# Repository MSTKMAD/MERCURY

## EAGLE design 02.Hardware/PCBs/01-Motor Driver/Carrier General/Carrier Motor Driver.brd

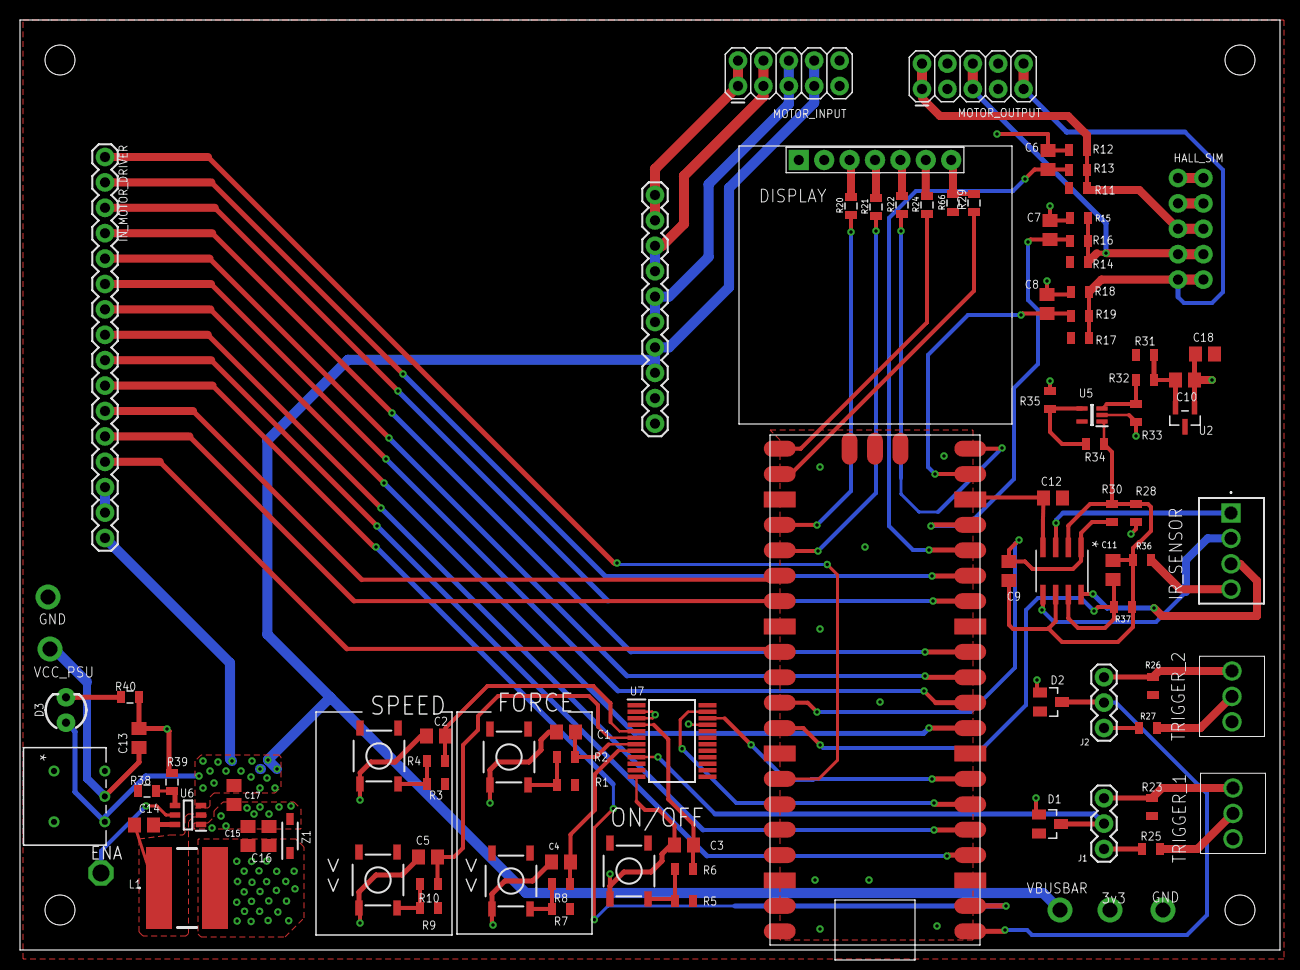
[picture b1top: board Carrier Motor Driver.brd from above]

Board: 2 copper layers, 126.0 x 93.0 mm, 88 parts (0 on the bottom side), 69 nets.

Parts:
C1, C2, C3, C4, C5, C6, C7, C8, C9, C10, C11, C12, C13, C14, C15, C16, C17, C18: C0805
D1, D2: BAT54S; SOT23
D3: LED_3MM
DISPLAY: Display; OLED_LCD
ENA: TESTPAD_TPSQPAD1-17; TESTPAD_P1-17
HALL_SIM: 2X5_NOSILK
IN_MOTOR_DRIVER: 1X16
IR_SENSOR: OSTVN04A150
J1, J2: 1X03
L1: SRN8040-8R2Y; SRN80408R2Y
MOTOR_INPUT: 2X5
MOTOR_OUTPUT: 2X5
OUT_MOTOR_DRIVER: 1X10
R1, R2, R3, R4, R5, R6, R7, R8, R9, R10, R11, R12, R13, R14, R15, R16, R17, R18, R19, R23, R25, R26, R27, R28, R30, R31, R32, R33, R34, R35, R36, R37: 0805
R20, R21, R22, R24, R29: 33; 0805
R38, R39, R40, R66: 10K; 0805
S1, S2, S3, S4, S5: MOMENTARY-SWITCH-SPST-SMD-5.2MM; TACTILE_SWITCH_SMD_5.2MM
TRIGGER_1, TRIGGER_2: OSTVN03A150
U1: MCP6002T-I/SN; SOIC8-N_MC_MCH
U2: LM4040BIM3-2.0/NOPB; DBZ3
U3: ATE1D-5M3-10-Z; SPDT05_ATE1D_9P5X8_NDC
U4: RPI_PICO
U5: MCP6001T-I_LT; SOT65P210X110-5N
U6: AP62200WU-7; SOT95P280X100-6N
U7: PCF8575DB; SOP65P780X200-24N
Z1: BZT52C3V6-7-F; SOD3716X135N

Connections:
CS: DISPLAY.7, R29.2, R66.2
D0: DISPLAY.3, R20.2
D1: DISPLAY.4, R21.2
DSP_RST: R22.1, U4.GP15
EN_0: IN_MOTOR_DRIVER.4, U4.GP9
EN_1: IN_MOTOR_DRIVER.2, U4.GP11
EN_2: IN_MOTOR_DRIVER.8, U4.GP3
EN_3: IN_MOTOR_DRIVER.6, U4.GP7
EN_4: IN_MOTOR_DRIVER.12, U4.GP21
EN_5: IN_MOTOR_DRIVER.10, U4.GP1
EN_DCDC: ENA.TP, U6.5
FRC_DOWN: C4.2, R8.1, U7.8
FRC_UP: C1.2, R2.1, U7.7
GND: C1.1, C2.1, C3.1, C4.1, C5.1, C6.1, C7.1, C8.1, C10.1, C12.1, C13.1, C15.1, C16.1, C17.2, C18.1, D1.1, D2.1, DISPLAY.1, HALL_SIM.3, HALL_SIM.4, IN_MOTOR_DRIVER.14, IN_MOTOR_DRIVER.15, IR_SENSOR.4, MOTOR_INPUT.9, MOTOR_INPUT.10, OUT_MOTOR_DRIVER.9, R12.1, R15.1, R18.1, R28.1, R33.2, R35.2, R36.1, R39.1, R40.1, S1.1, S2.1, S3.1, S4.1, S5.1, TRIGGER_1.3, TRIGGER_2.3, U1.4, U2.1, U4.GND@1, U4.GND@2, U4.GND@3, U4.GND@4, U4.GND@6, U4.GND@7, U4.GND@8, U5.2, U6.1, U7.2, U7.3, U7.12, U7.21, Z1.2
HALL_A: HALL_SIM.5, HALL_SIM.6, MOTOR_OUTPUT.1, MOTOR_OUTPUT.2, R11.1, R12.2, R13.2
HALL_B: HALL_SIM.7, HALL_SIM.8, MOTOR_OUTPUT.5, MOTOR_OUTPUT.6, R14.1, R15.2, R16.2
HALL_C: HALL_SIM.9, HALL_SIM.10, MOTOR_OUTPUT.9, MOTOR_OUTPUT.10, R17.1, R18.2, R19.2
IN_SENSOR_1: IR_SENSOR.1, U1.3
IN_SENSOR_2: IR_SENSOR.2, U1.5
ISENSE: IN_MOTOR_DRIVER.1, U4.GP28_A2
MISO: R24.1, U4.GP16
MOSI: R21.1, U4.GP19
MOTOR_A: MOTOR_INPUT.1, MOTOR_INPUT.2, OUT_MOTOR_DRIVER.1, OUT_MOTOR_DRIVER.2
MOTOR_B: MOTOR_INPUT.3, MOTOR_INPUT.4, OUT_MOTOR_DRIVER.3, OUT_MOTOR_DRIVER.4
MOTOR_C: MOTOR_INPUT.5, MOTOR_INPUT.6, OUT_MOTOR_DRIVER.5, OUT_MOTOR_DRIVER.6
unnamed: R1.1, R2.2, S1.3
unnamed: R3.1, R4.2, S2.3
unnamed: R5.1, R6.2, S3.3
unnamed: R34.2, R35.1, U5.4
unnamed: R7.1, R8.2, S4.3
unnamed: R32.2, R33.1, U5.3
unnamed: R9.1, R10.2, S5.3
unnamed: C10.2, R31.1, R32.1, U2.2
unnamed: DISPLAY.6, R24.2
unnamed: J2.3, R26.2, TRIGGER_2.1
unnamed: R27.2, TRIGGER_2.2
unnamed: J1.3, R23.2, TRIGGER_1.1
unnamed: R25.2, TRIGGER_1.2
unnamed: J2.1, R27.1
unnamed: J1.1, R25.1
unnamed: D3.K, R40.2
unnamed: C14.2, U6.6
unnamed: C14.1, L1.1, U6.2
unnamed: R38.1, R39.2, U6.4
ON/OFF: C3.2, R6.1, U7.4
PWM_IN_0: IN_MOTOR_DRIVER.5, U4.GP8
PWM_IN_1: IN_MOTOR_DRIVER.3, U4.GP10
PWM_IN_2: IN_MOTOR_DRIVER.9, U4.GP2
PWM_IN_3: IN_MOTOR_DRIVER.7, U4.GP6
PWM_IN_4: IN_MOTOR_DRIVER.13, U4.GP22
PWM_IN_5: IN_MOTOR_DRIVER.11, U4.GP20
RST: DISPLAY.5, R22.2
SCK: R20.1, U4.GP18
SCL: U4.GP5, U7.22
SDA: U4.GP4, U7.23
SENSOR_1: C9.1, R30.2, U1.1, U4.GP26_A0
SENSOR_2: C11.1, R37.2, U1.7, U4.GP27_A1
SENSOR_A: C6.2, R13.1, U4.GP12
SENSOR_B: C7.2, R16.1, U4.GP13
SENSOR_C: C8.2, R19.1, U4.GP14
SPD_DOWN: C5.2, R10.1, U7.6
SPD_UP: C2.2, R4.1, U7.5
SS: R29.1, U4.GP17
T1: D1.3, J1.2, U7.9
T2: D2.3, J2.2, U4.GP0
VBUSBAR: C17.1, D3.A, IN_MOTOR_DRIVER.16, MOTOR_INPUT.7, MOTOR_INPUT.8, OUT_MOTOR_DRIVER.7, OUT_MOTOR_DRIVER.8, U3.1, U6.3
VCC: C12.2, C15.2, C16.2, C18.2, D1.2, D2.2, DISPLAY.2, HALL_SIM.1, HALL_SIM.2, IR_SENSOR.3, L1.2, OUT_MOTOR_DRIVER.10, R1.2, R3.2, R5.2, R7.2, R9.2, R11.2, R14.2, R17.2, R23.1, R26.1, R31.2, R38.2, R66.1, U1.8, U4.VBUS, U5.5, U7.24, Z1.1
VCC_PSU: C13.2, U3.2
V_COMP: C9.2, C11.2, R28.2, R30.1, R34.1, R36.2, R37.1, U1.2, U1.6, U5.1

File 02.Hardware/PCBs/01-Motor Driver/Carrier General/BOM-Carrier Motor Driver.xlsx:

BOM Version | 1
 | Carrier Motor Driver
Position | Qty | Part | Value | Device | Package | Unit Price | Extended Price | Link | Assembly
1 | 6 | C1, C2, C3, C4, C5, C14 | 100n | CAPACITOR | SMD 0805
2 | 3 | C6, C7, C8 | 10n | CAPACITOR | SMD 0805
3 | 2 | C13, C17 | 10uF | CAPACITOR | SMD 0805
4 | 2 | C15, C16 | 22uF | CAPACITOR | SMD 0805
5 | 5 | C9, C10, C11, C12, C18 | N.C. | CAPACITOR | SMD 0805
6 | 2 | J1, J2 |  | CONNECTOR | 1X03
7 | 1 | HALL_SIM |  | CONNECTOR | 2X5_NOSILK
8 | 2 | MOTOR_INPUT, MOTOR_OUTPUT |  | CONNECTOR | 2X5
9 | 1 | IN_MOTOR_DRIVER |  | CONNECTOR | 1X16
10 | 2 | TRIGGER_1, TRIGGER_2 | OSTVN03A150 | CONNECTOR | OSTVN03A150
11 | 1 | IR_SENSOR | OSTVN04A150 | CONNECTOR | OSTVN04A150
12 | 1 | D3 |  | DIODE | LED_3MM
13 | 2 | D1, D2 | BAT54S | DIODE | SOT23
14 | 1 | L1 | SRN8040-8R2Y | INDUCTANCE | SRN80408R2Y
15 | 1 | U6 | AP62200WU-7 | INTEGRATED CIRCUIT | SOT95P280X100-6N
16 | 1 | U3 | ATE1D-5M3-10-Z | SWITCH | SPDT05_ATE1D_9P5X8_NDC
17 | 1 | Z1 | BZT52C3V6-7-F | INTEGRATED CIRCUIT | SOD3716X135N
18 | 1 | U2 | LM4040BIM3-2.0/NOPB | INTEGRATED CIRCUIT | DBZ3
19 | 1 | U5 | MCP6001T-I_LT | INTEGRATED CIRCUIT | SOT65P210X110-5N
20 | 1 | U1 | MCP6002T-I/SN | INTEGRATED CIRCUIT | SOIC8-N_MC_MCH
21 | 1 | U7 | PCF8575DB | INTEGRATED CIRCUIT | SOP65P780X200-24N
22 | 1 | DISPLAY | Display | OLED_LCD | OLED_LCD
23 | 1 | U4 | CPU | RASPBERRY PI PICO | RPI_PICO
24 | 3 | R13, R16, R19 | 100R | RESISTOR | SMD 0805
25 | 2 | R39, R66 | 10K | RESISTOR | SMD 0805
26 | 5 | R2, R4, R6, R8, R10 | 1K | RESISTOR | SMD 0805
27 | 1 | R40 | 1K2 | RESISTOR | SMD 0805
28 | 5 | R1, R3, R5, R7, R9 | 22K | RESISTOR | SMD 0805
29 | 3 | R11, R14, R17 | 2K2 | RESISTOR | SMD 0805
30 | 5 | R20, R21, R22, R24, R29 | 33R | RESISTOR | SMD 0805
31 | 1 | R38 | 36K1 | RESISTOR | SMD 0805
32 | 16 | R12, R15, R18, R23, R25, R26, R27, R28, R30, R31, R32, R33, R34, R35, R36, R37 | N.C. | RESISTOR | SMD 0805
33 | 5 | S1, S2, S3, S4, S5 | MOMENTARY-SWITCH-SPST-SMD-5.2MM | SWITCH | TACTILE_SWITCH_SMD_5.2MM

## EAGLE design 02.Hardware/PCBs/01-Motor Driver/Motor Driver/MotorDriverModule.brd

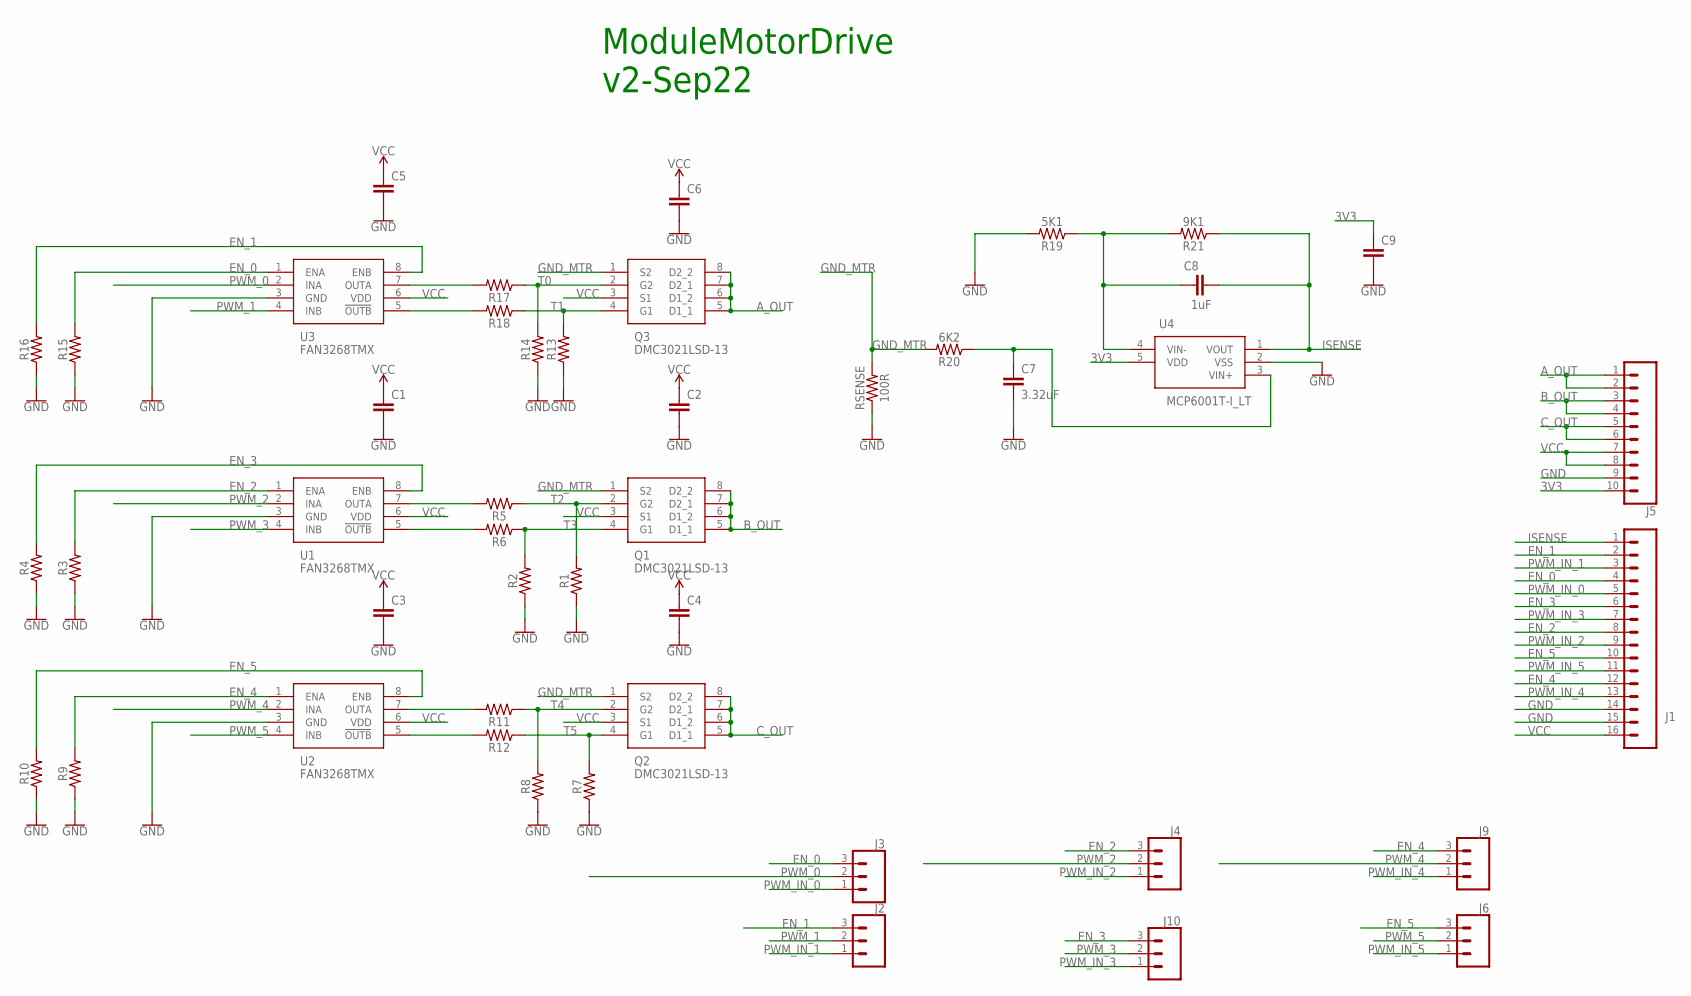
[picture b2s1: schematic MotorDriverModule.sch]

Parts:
C1, C2, C3, C4, C5, C6, C9: C-EUC0805; C0805
C7: 3.32uF; C0805
C8: 1uF; C0805
J1: CONN_16; 1X16
J2, J3, J4, J6, J9, J10: CONN_03; 1X03
J5: CONN_10"; 1X10
Q1, Q2, Q3: DMC3021LSD-13; SOIC127P600X175-8N
R1, R2, R3, R4, R5, R6, R7, R8, R9, R10, R11, R12, R13, R14, R15, R16, R17, R18: 0805
R19: 5K1; 0805
R20: 6K2; 0805
R21: 9K1; 0805
RSENSE: 100R; 1206
U1, U2, U3: FAN3268TMX; SOIC127P600X175-8N
U4: MCP6001T-I_LT; SOT65P210X110-5N

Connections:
3V3: C9.1, J5.10, U4.5 (VDD)
A_OUT: J5.1, J5.2, Q3.5 (D1_1), Q3.6 (D1_2), Q3.7 (D2_1), Q3.8 (D2_2)
B_OUT: J5.3, J5.4, Q1.5 (D1_1), Q1.6 (D1_2), Q1.7 (D2_1), Q1.8 (D2_2)
C_OUT: J5.5, J5.6, Q2.5 (D1_1), Q2.6 (D1_2), Q2.7 (D2_1), Q2.8 (D2_2)
EN_0: J1.4, J3.3, R15.2, U3.1 (ENA)
EN_1: J1.2, J2.3, R16.2, U3.8 (ENB)
EN_2: J1.8, J4.3, R3.2, U1.1 (ENA)
EN_3: J1.6, J10.3, R4.2, U1.8 (ENB)
EN_4: J1.12, J9.3, R9.2, U2.1 (ENA)
EN_5: J1.10, J6.3, R10.2, U2.8 (ENB)
GND: C1.2, C2.2, C3.2, C4.2, C5.2, C6.2, C7.2, C9.2, J1.14, J1.15, J5.9, R1.1, R2.1, R3.1, R4.1, R7.1, R8.1, R9.1, R10.1, R13.1, R14.1, R15.1, R16.1, R19.2, RSENSE.1, U1.3 (GND), U2.3 (GND), U3.3 (GND), U4.2 (VSS)
GND_MTR: Q1.1 (S2), Q2.1 (S2), Q3.1 (S2), R20.2, RSENSE.2
ISENSE: C8.2, J1.1, R21.1, U4.1 (VOUT)
unnamed: C8.1, R19.1, R21.2, U4.4 (VIN-)
unnamed: C7.1, R20.1, U4.3 (VIN+)
unnamed: R6.2, U1.5 (!OUTB)
unnamed: R5.2, U1.7 (OUTA)
unnamed: R12.2, U2.5 (!OUTB)
unnamed: R11.2, U2.7 (OUTA)
unnamed: R18.2, U3.5 (!OUTB)
unnamed: R17.2, U3.7 (OUTA)
PWM_0: J3.2, U3.2 (INA)
PWM_1: J2.2, U3.4 (INB)
PWM_2: J4.2, U1.2 (INA)
PWM_3: J10.2, U1.4 (INB)
PWM_4: J9.2, U2.2 (INA)
PWM_5: J6.2, U2.4 (INB)
PWM_IN_0: J1.5, J3.1
PWM_IN_1: J1.3, J2.1
PWM_IN_2: J1.9, J4.1
PWM_IN_3: J1.7, J10.1
PWM_IN_4: J1.13, J9.1
PWM_IN_5: J1.11, J6.1
T0: Q3.2 (G2), R14.2, R17.1
T1: Q3.4 (G1), R13.2, R18.1
T2: Q1.2 (G2), R1.2, R5.1
T3: Q1.4 (G1), R2.2, R6.1
T4: Q2.2 (G2), R8.2, R11.1
T5: Q2.4 (G1), R7.2, R12.1
VCC: C1.1, C2.1, C3.1, C4.1, C5.1, C6.1, J1.16, J5.7, J5.8, Q1.3 (S1), Q2.3 (S1), Q3.3 (S1), U1.6 (VDD), U2.6 (VDD), U3.6 (VDD)

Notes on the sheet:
ModuleMotorDrive v2-Sep22

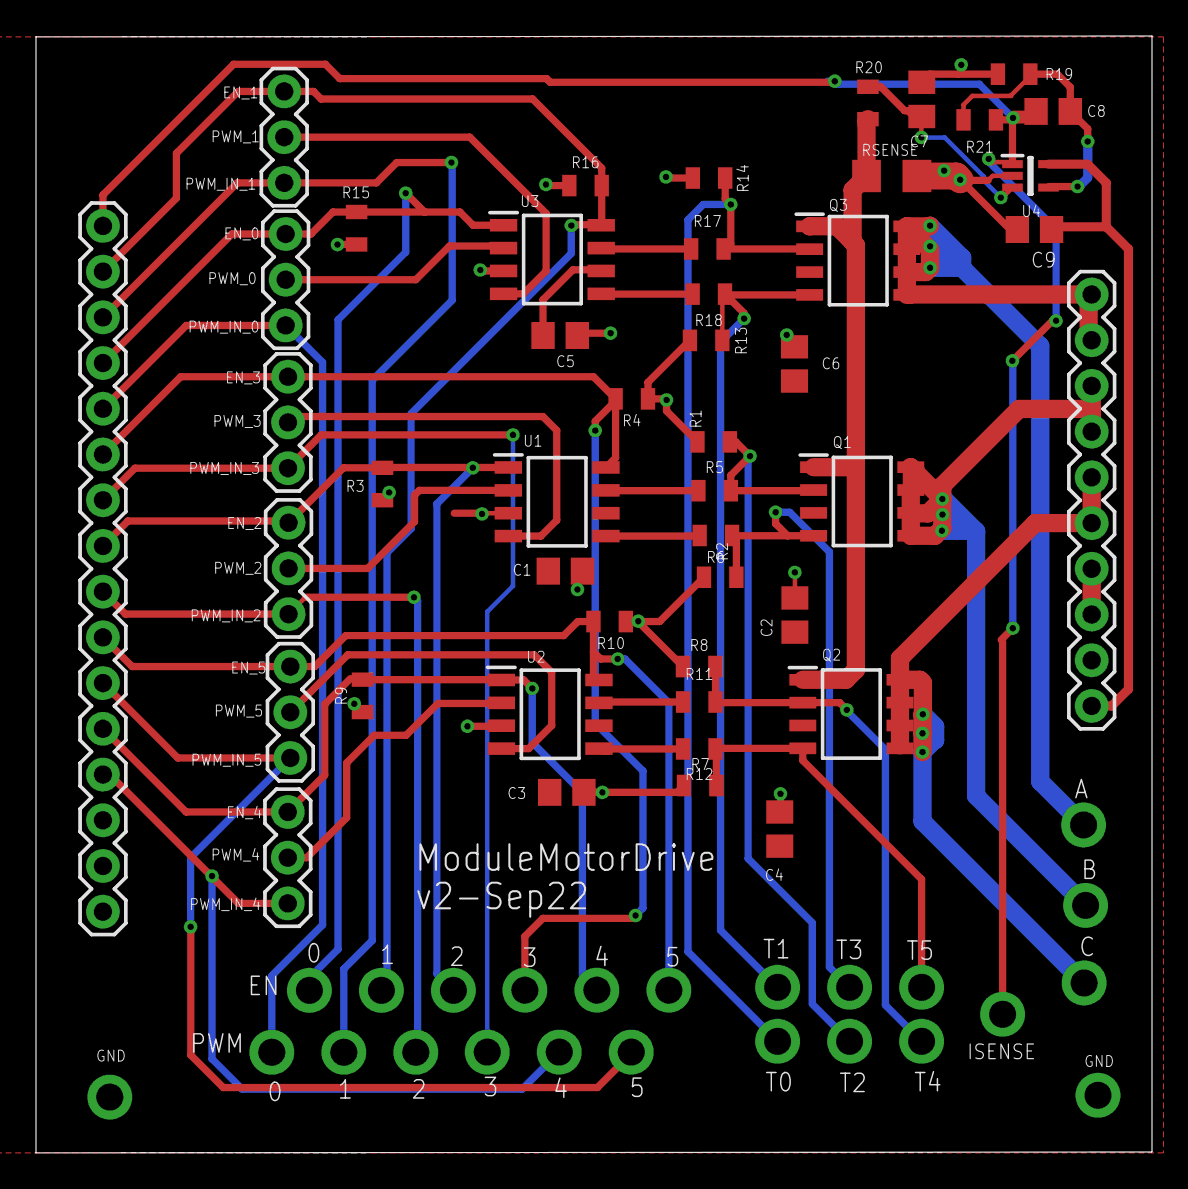
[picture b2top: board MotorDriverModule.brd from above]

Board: 2 copper layers, 62.0 x 62.0 mm, 46 parts (0 on the bottom side), 40 nets.

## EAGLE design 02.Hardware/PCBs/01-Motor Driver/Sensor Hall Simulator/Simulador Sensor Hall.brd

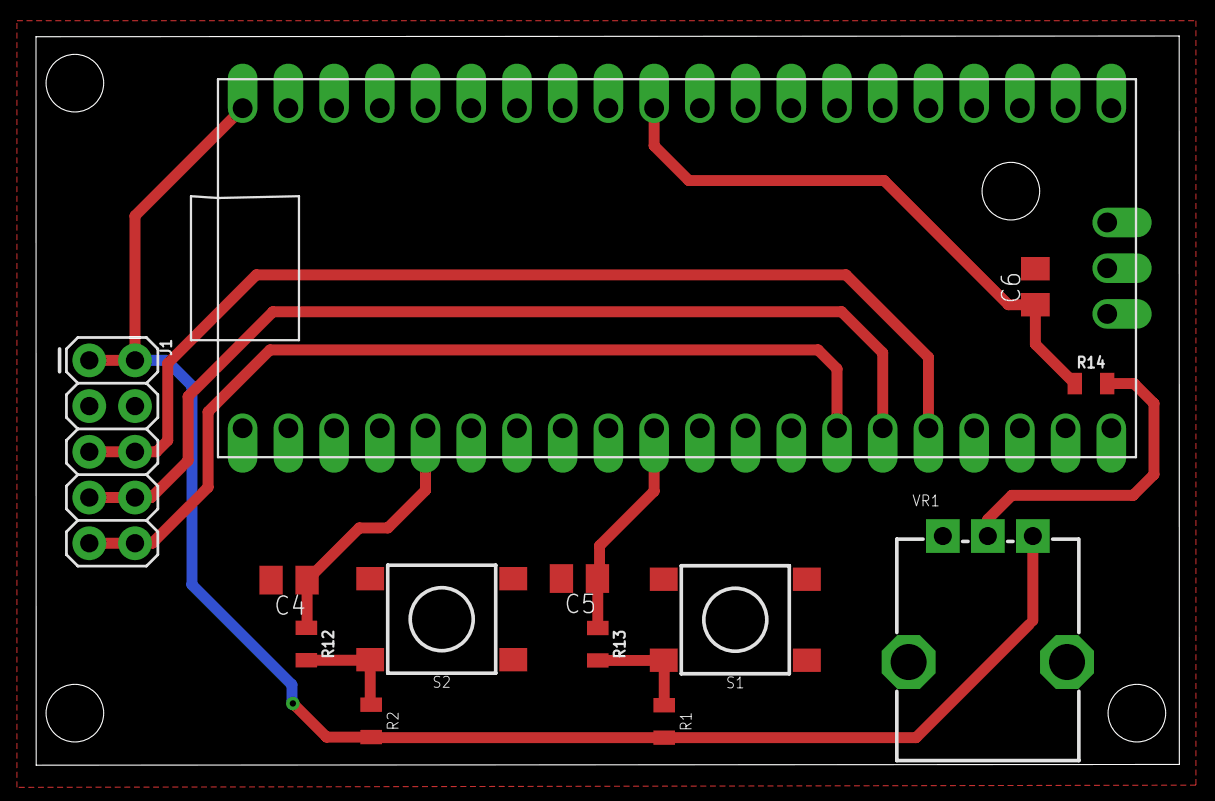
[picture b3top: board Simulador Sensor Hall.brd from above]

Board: 2 copper layers, 63.5 x 40.5 mm, 13 parts (0 on the bottom side), 11 nets.

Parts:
C4, C5, C6: C0805K
J1: 2X5
R1, R2, R12, R13, R14: 0805
S1, S2: MOMENTARY-SWITCH-SPST-SMD-6.2MM-TALL; TACTILE_SWITCH_SMD_6.2MM_TALL
VR1: 10k; POT-PTH-ALPS
X1: RPI_PICO_TH

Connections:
DIR: C5.1, R13.1, X1.GP7
GND: C4.2, C5.2, C6.2, J1.3, J1.4, S1.A2, S2.A2, VR1.P$3, X1.GND@5
HALL_A: J1.5, J1.6, X1.GP12
HALL_B: J1.7, J1.8, X1.GP11
HALL_C: J1.9, J1.10, X1.GP10
unnamed: R2.1, R12.2, S2.B2
unnamed: R1.1, R13.2, S1.B2
unnamed: R14.2, VR1.P$2
SPEED: C6.1, R14.1, X1.GP26_A0
START_STOP: C4.1, R12.1, X1.GP3
VCC: J1.1, J1.2, R1.2, R2.2, VR1.P$1, X1.VBUS

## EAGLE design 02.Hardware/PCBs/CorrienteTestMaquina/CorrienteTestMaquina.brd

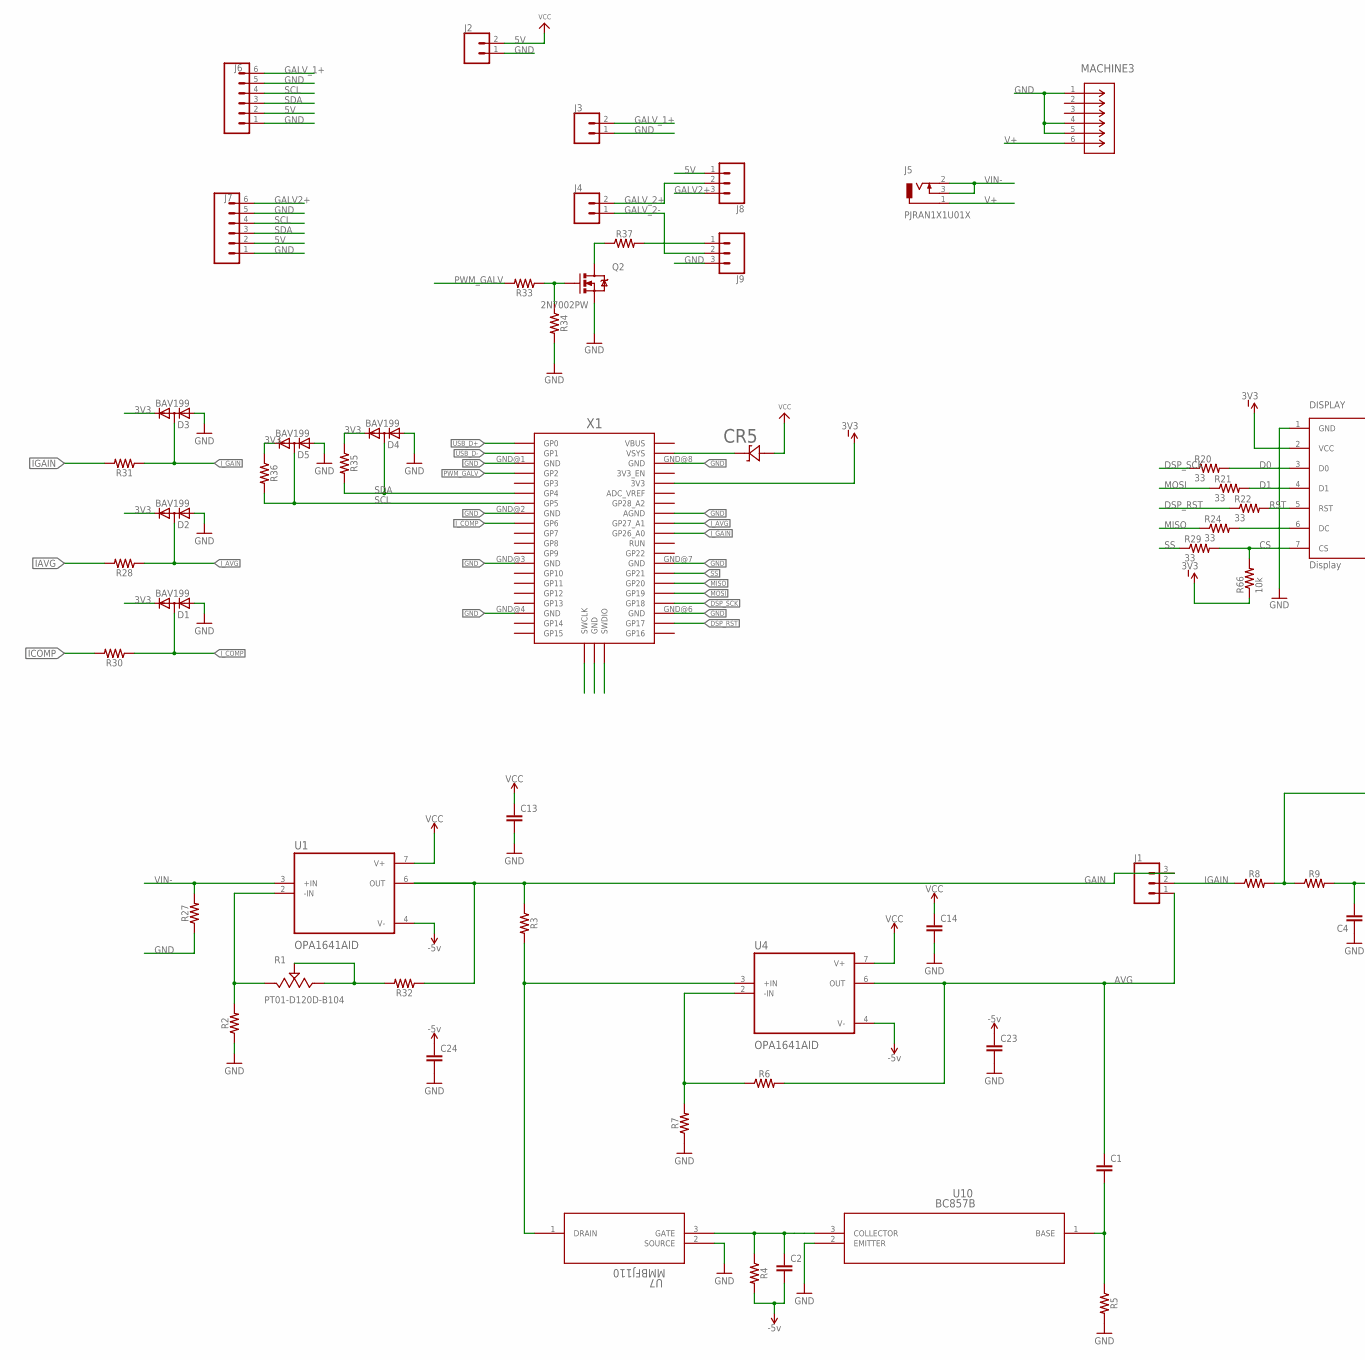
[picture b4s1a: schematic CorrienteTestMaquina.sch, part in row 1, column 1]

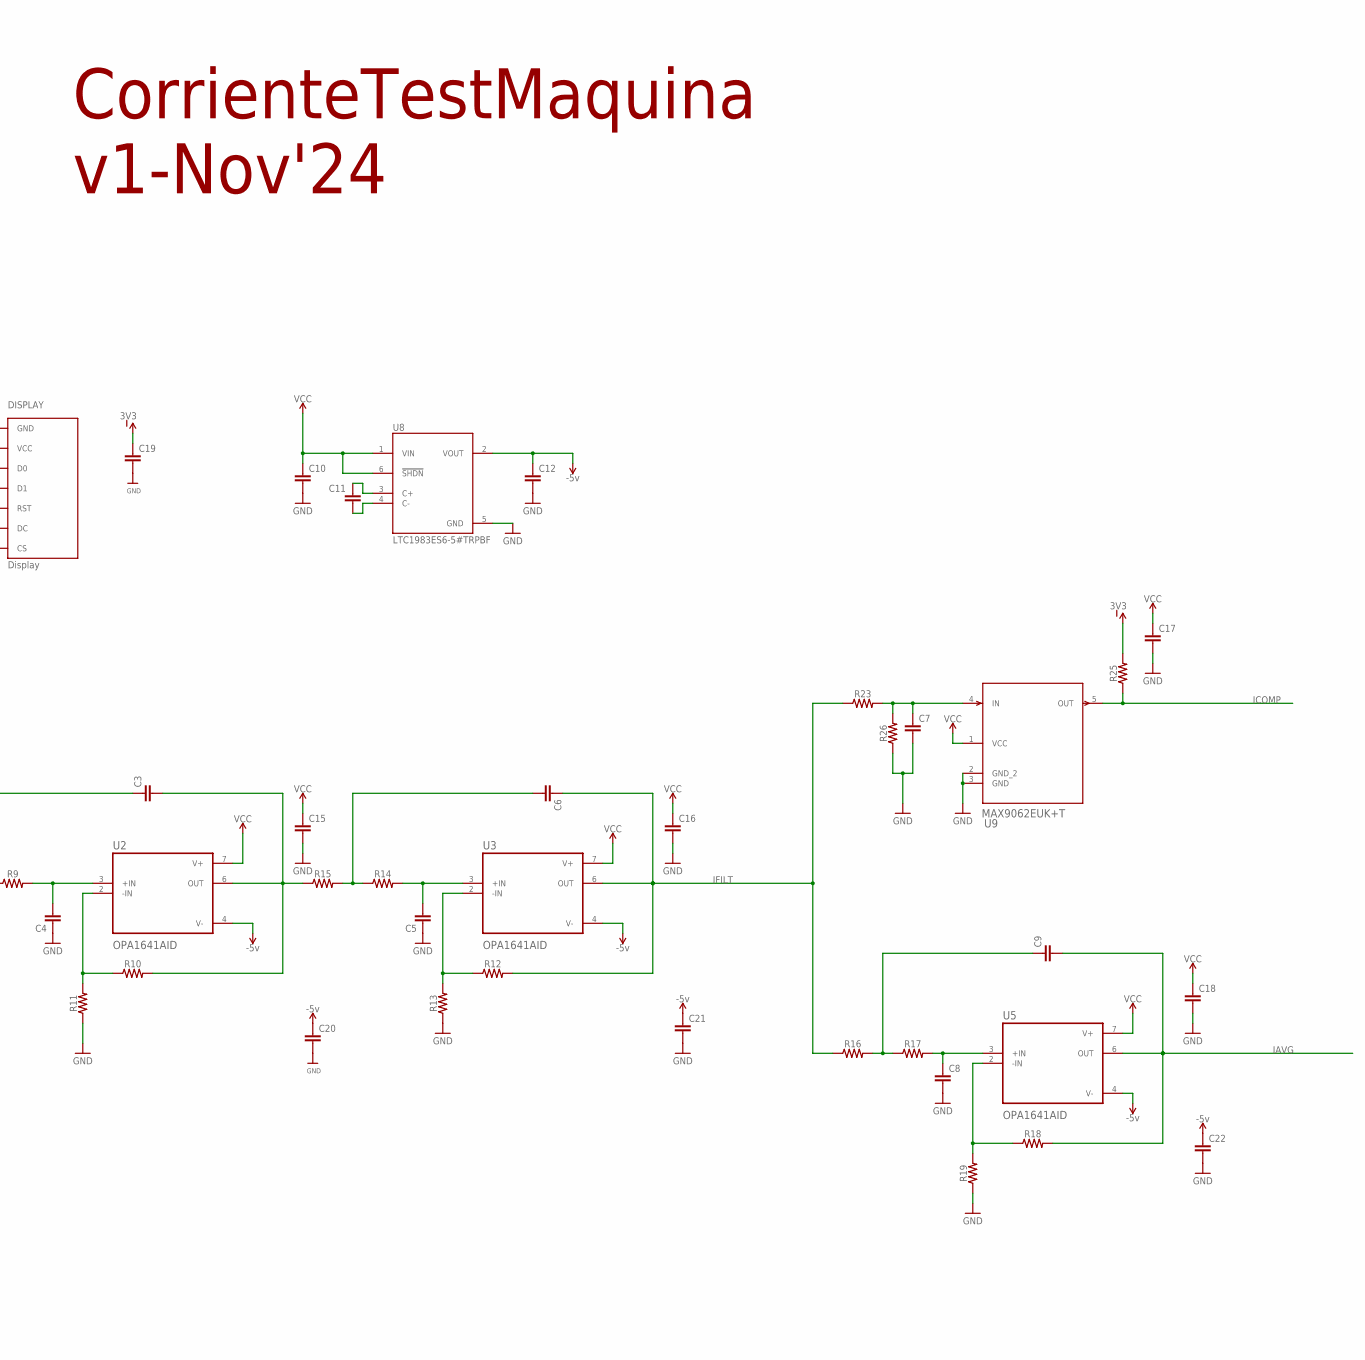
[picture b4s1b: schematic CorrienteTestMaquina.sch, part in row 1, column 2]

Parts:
C1, C2, C3, C4, C5, C6, C7, C8, C9, C10, C11, C12, C13, C14, C15, C16, C17, C18, C19, C20, C21, C22, C23, C24: CAP0805; 0805
CR5: STPS1L40U; SMB_STM
D1, D2, D3, D4, D5: BAV199; SOT23
DISPLAY: Display; OLED_LCD
J1, J8, J9: CONN_03; 1X03
J2, J3, J4: CONN_02; 1X02
J5: PJRAN1X1U01X
J6, J7: CONN_06SILK_FEMALE_PTH; 1X06
MACHINE3: ACJS-MHDR; CONN_MHDR_AMP
Q2: 2N7002PW; SOT323
R1: PT01-D120D-B104; TRIM_PT01-D120D-B104
R2, R3, R4, R5, R6, R7, R8, R9, R10, R11, R12, R13, R14, R15, R16, R17, R18, R19, R23, R25, R26, R28, R30, R31, R32, R33, R34, R35, R36, R37: 0805
R20, R21, R22, R24, R29: 33; 0805
R27: 1206
R66: 10k; 0805
U1, U2, U3, U4, U5: OPA1641AID; SOIC127P599X175-8N
U7: MMBFJ110; SSOT3_3X1P5_ONS
U8: LTC1983ES6-5#TRPBF; SOT95P280X100-6N
U9: MAX9062EUK+T; 21-0057F_MXM
U10: BC857B; SOT23_NXP
X1: RPI_PICO_IG-TH; RPI_PICO_TH

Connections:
3V3: C19.1, D1.2 (C), D2.2 (C), D3.2 (C), D4.2 (C), D5.2 (C), DISPLAY.2 (VCC), R25.2, R35.1, R36.1, R66.1, X1.3V3
5V: C10.1, C13.1, C14.1, C15.1, C16.1, C17.1, C18.1, CR5.1, J2.2, J6.2, J7.2, J8.1, U1.7 (V+), U2.7 (V+), U3.7 (V+), U4.7 (V+), U5.7 (V+), U8.1 (VIN), U8.6 (!SHDN), U9.1 (VCC)
-5V: C2.2, C12.1, C20.1, C21.1, C22.1, C23.1, C24.1, R4.2, U1.4 (V-), U2.4 (V-), U3.4 (V-), U4.4 (V-), U5.4 (V-), U8.2 (VOUT)
AVG: C1.1, J1.1, R6.2, U4.6 (OUT)
CS: DISPLAY.7 (CS), R29.2, R66.2
D0: DISPLAY.3 (D0), R20.2
D1: DISPLAY.4 (D1), R21.2
DSP_RST: R22.1, X1.GP17
DSP_SCK: R20.1, X1.GP18
GAIN: J1.3, R3.1, R32.1, U1.6 (OUT)
GALV2+: J7.6, J8.3
GALV_1+: J3.2, J6.6
GALV_2+: J4.2, J8.2
GALV_2-: J4.1, J9.2
GND: C4.1, C5.1, C7.2, C8.2, C10.2, C12.2, C13.2, C14.2, C15.2, C16.2, C17.2, C18.2, C19.2, C20.2, C21.2, C22.2, C23.2, C24.2, D1.1 (A), D2.1 (A), D3.1 (A), D4.1 (A), D5.1 (A), DISPLAY.1 (GND), J2.1, J3.1, J6.1, J6.5, J7.1, J7.5, J9.3, MACHINE3.1, MACHINE3.4, MACHINE3.5, Q2.2 (S), R2.1, R5.2, R7.1, R11.1, R13.1, R19.1, R26.1, R27.1, R34.2, U7.2 (SOURCE), U8.5 (GND), U9.2 (GND_2), U9.3 (GND), U10.2 (EMITTER), X1.AGND, X1.GND@1 (GND), X1.GND@2 (GND), X1.GND@3 (GND), X1.GND@4 (GND), X1.GND@6 (GND), X1.GND@7 (GND), X1.GND@8 (GND)
IAVG: C9.2, R18.2, R28.2, U5.6 (OUT)
ICOMP: R25.1, R30.2, U9.5 (OUT)
IFILT: C6.1, R12.2, R16.1, R23.1, U3.6 (OUT)
IGAIN: J1.2, R8.1, R31.2
I_AVG: D2.3 (AC), R28.1, X1.GP27_A1
I_COMP: D1.3 (AC), R30.1, X1.GP6
I_GAIN: D3.3 (AC), R31.1, X1.GP26_A0
MISO: R24.1, X1.GP20
MOSI: R21.1, X1.GP19
unnamed: Q2.1 (G), R33.1, R34.1
unnamed: R1.1, R2.2, U1.2 (-IN)
unnamed: J9.1, R37.2
unnamed: C2.1, R4.1, U7.3 (GATE), U10.3 (COLLECTOR)
unnamed: C1.2, R5.1, U10.1 (BASE)
unnamed: Q2.3 (D), R37.1
unnamed: DISPLAY.6 (DC), R24.2
unnamed: R6.1, R7.2, U4.2 (-IN)
unnamed: C3.1, R8.2, R9.1
unnamed: C4.2, R9.2, U2.3 (+IN)
unnamed: R10.1, R11.2, U2.2 (-IN)
unnamed: C3.2, R10.2, R15.1, U2.6 (OUT)
unnamed: C6.2, R14.1, R15.2
unnamed: C5.2, R14.2, U3.3 (+IN)
unnamed: R12.1, R13.2, U3.2 (-IN)
unnamed: R1.2, R1.3, R32.2
unnamed: C8.1, R17.2, U5.3 (+IN)
unnamed: C9.1, R16.2, R17.1
unnamed: R18.1, R19.2, U5.2 (-IN)
unnamed: C7.1, R23.2, R26.2, U9.4 (IN)
unnamed: R3.2, U4.3 (+IN), U7.1 (DRAIN)
unnamed: C11.1, U8.3 (C+)
unnamed: C11.2, U8.4 (C-)
unnamed: CR5.2, X1.VSYS
PWM_GALV: R33.2, X1.GP2
RST: DISPLAY.5 (RST), R22.2
SCL: D5.3 (AC), J6.4, J7.4, R36.2, X1.GP5
SDA: D4.3 (AC), J6.3, J7.3, R35.2, X1.GP4
SS: R29.1, X1.GP21
USB_D+: X1.GP0
USB_D-: X1.GP1
V+: J5.1, MACHINE3.6
VIN-: J5.2, J5.3, R27.2, U1.3 (+IN)

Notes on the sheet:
CorrienteTestMaquina v1-Nov'24

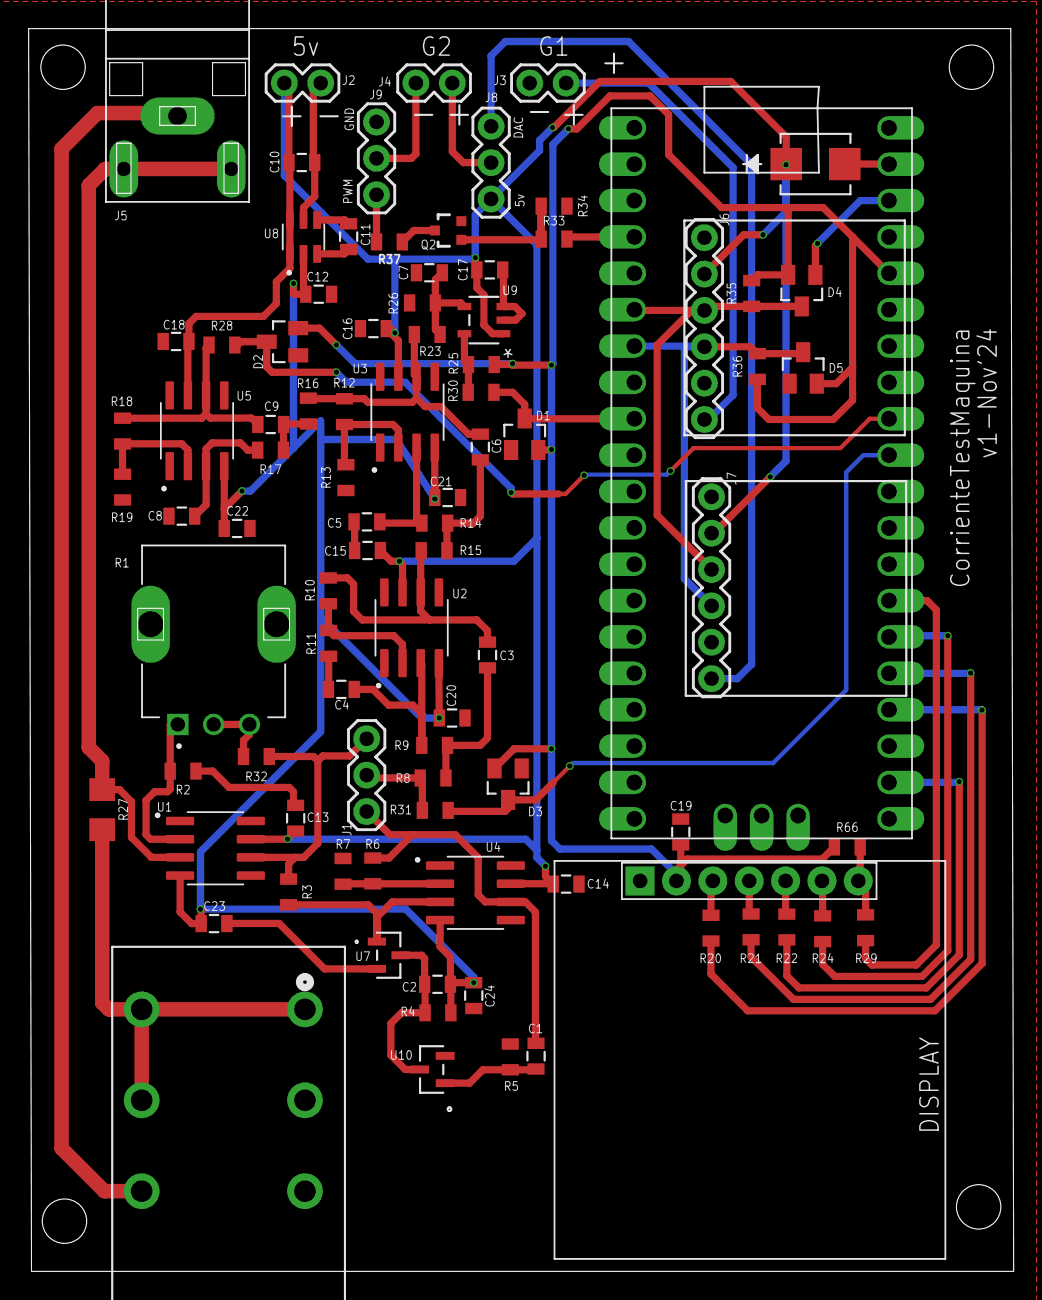
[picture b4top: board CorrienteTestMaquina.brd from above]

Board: 2 copper layers, 68.8 x 86.8 mm, 90 parts (0 on the bottom side), 55 nets.

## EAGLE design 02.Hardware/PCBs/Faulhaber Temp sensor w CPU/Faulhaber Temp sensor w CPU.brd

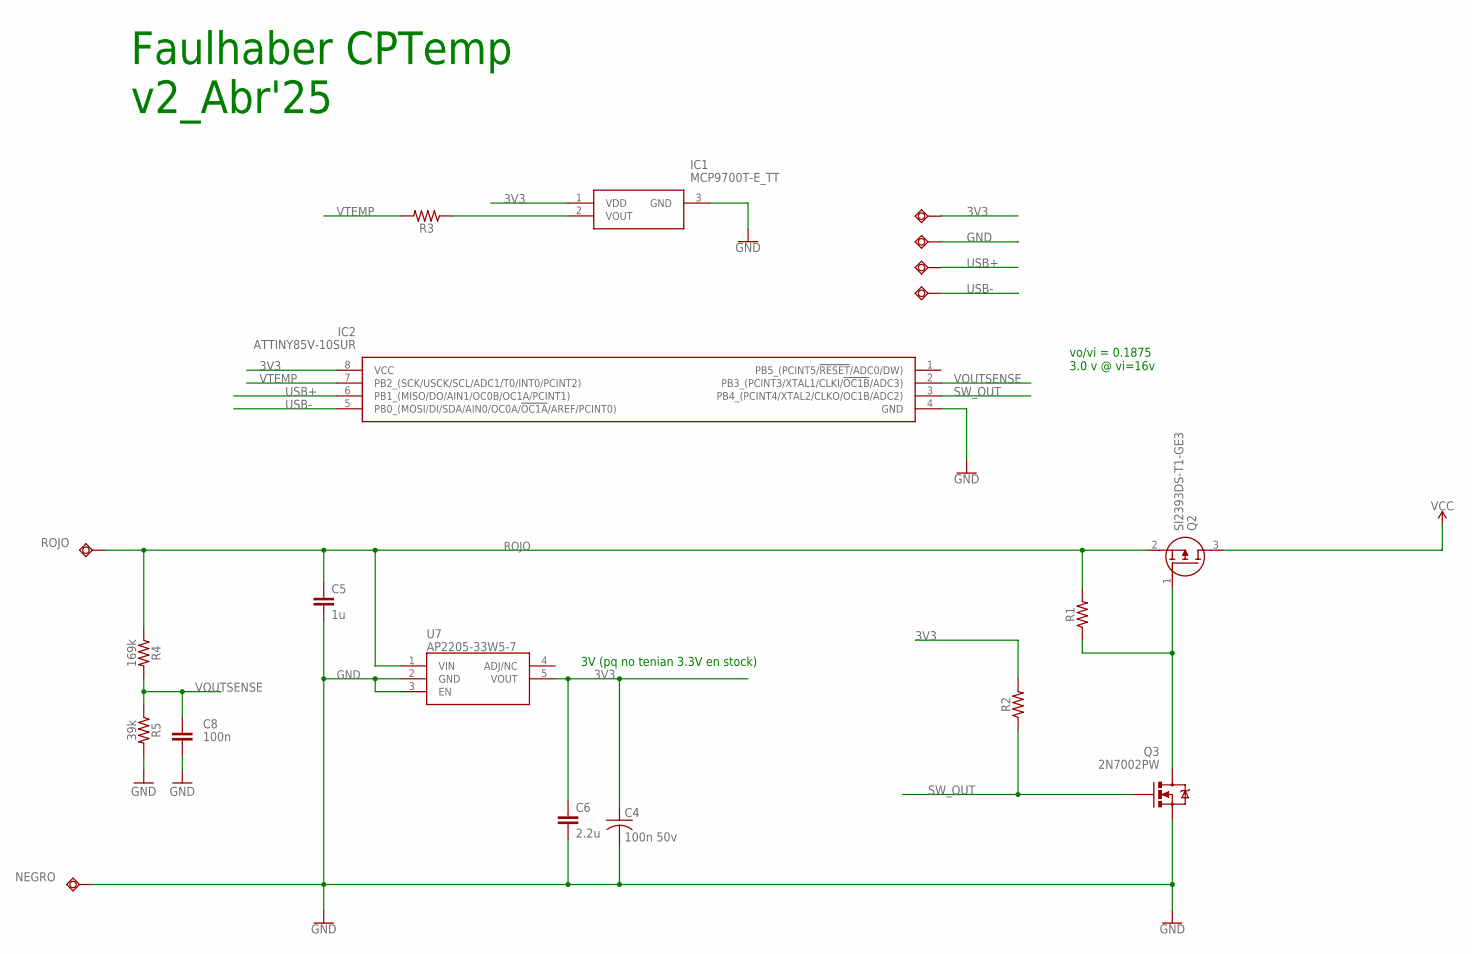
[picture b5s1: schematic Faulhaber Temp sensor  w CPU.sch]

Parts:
3V3: TESTPAD_TPSQB1,27; TESTPAD_B1,27
C4: 100n 50v; C0805
C5: 1u; 0603-CAP
C6: 2.2u; 0603-CAP
C8: 100n; 0603
GND: TESTPAD_TPSQB1,27; TESTPAD_B1,27
IC1: MCP9700T-E_TT; SOT95P237X112-3N
IC2: ATTINY85V-10SUR; SOIC127P798X216-8N
NEGRO: TESTPAD_TPSQTP10SQ; TESTPAD_TP10SQ
Q2: SI2393DS-T1-GE3; SOT95P237X112-3N
Q3: 2N7002PW; SOT323
R1, R2, R3: 0603
R4: 169k; 0603
R5: 39k; 0603
ROJO: TESTPAD_TPSQTP10SQ; TESTPAD_TP10SQ
U7: AP2205-33W5-7; SOT95P282X145-5N
USB+: TESTPAD_TPSQB1,27; TESTPAD_B1,27
USB-: TESTPAD_TPSQB1,27; TESTPAD_B1,27

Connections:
3V3: 3V3.TP, C4.1, C6.1, IC1.1 (VDD), IC2.8 (VCC), R2.2, U7.5 (VOUT)
GND: C4.2, C5.2, C6.2, C8.2, GND.TP, IC1.3 (GND), IC2.4 (GND), NEGRO.TP, Q3.2 (S), R5.2, U7.2 (GND), U7.3 (EN)
unnamed: IC1.2 (VOUT), R3.1
unnamed: Q2.1 (G), Q3.3 (D), R1.1
ROJO: C5.1, Q2.2 (S), R1.2, R4.1, ROJO.TP, U7.1 (VIN)
SW_OUT: IC2.3 (PB4_(PCINT4/XTAL2/CLKO/OC1B/ADC2)), Q3.1 (G), R2.1
USB+: IC2.6 (PB1_(MISO/DO/AIN1/OC0B/OC1A/PCINT1)), USB+.TP
USB-: IC2.5 (PB0_(MOSI/DI/SDA/AIN0/OC0A/!OC1A!/AREF/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), USB-.TP
VCC: Q2.3 (D)
VOUTSENSE: C8.1, IC2.2 (PB3_(PCINT3/XTAL1/CLKI/!OC1B!/ADC3)), R4.2, R5.1
VTEMP: IC2.7 (PB2_(SCK/USCK/SCL/ADC1/T0/INT0/PCINT2)), R3.2

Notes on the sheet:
3V (pq no tenian 3.3V en stock)
Faulhaber CPTemp v2_Abr'25
vo/vi = 0.1875 3.0 v @ vi=16v

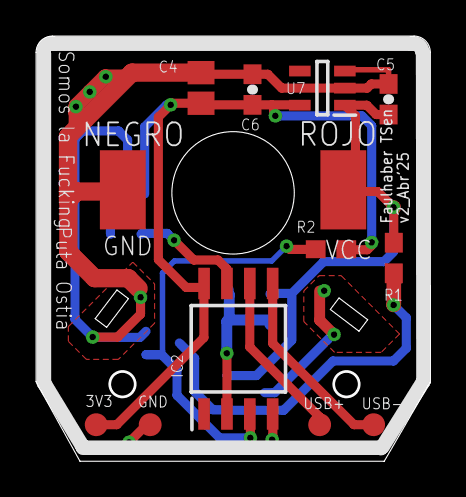
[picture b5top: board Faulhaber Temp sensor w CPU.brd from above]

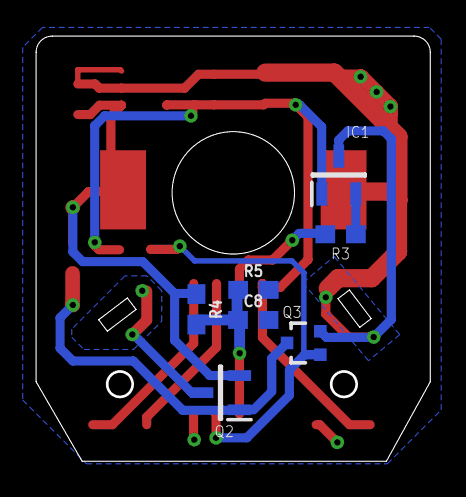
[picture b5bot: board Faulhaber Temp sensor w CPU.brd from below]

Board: 2 copper layers, 21.9 x 23.6 mm, 20 parts (7 on the bottom side), 10 nets.

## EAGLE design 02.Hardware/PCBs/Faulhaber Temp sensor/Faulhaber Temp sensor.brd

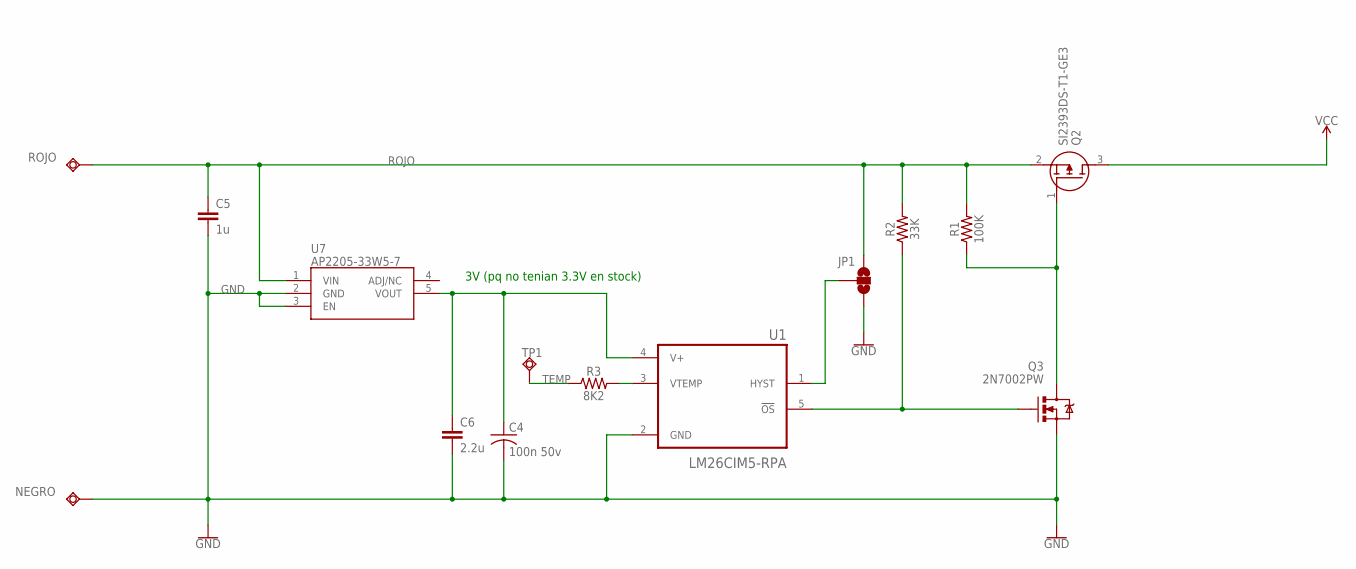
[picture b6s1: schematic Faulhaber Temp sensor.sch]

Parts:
C4: 100n 50v; C0805
C5: 1u; 0603-CAP
C6: 2.2u; 0603-CAP
JP1: JUMPER-SMT_3_NO_SILK; SMT-JUMPER_3_NO_SILK
NEGRO: TESTPAD_TPSQTP10SQ; TESTPAD_TP10SQ
Q2: SI2393DS-T1-GE3; SOT95P237X112-3N
Q3: 2N7002PW; SOT323
R1: 100K; 0603
R2: 33K; 0603
R3: 8K2; 0603
ROJO: TESTPAD_TPSQTP10SQ; TESTPAD_TP10SQ
TP1: TESTPAD_TPSQTP20R; TESTPAD_TP20R
U1: LM26CIM5-RPA; SOT95P280X145-5N
U7: AP2205-33W5-7; SOT95P282X145-5N

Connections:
GND: C4.2, C5.2, C6.2, JP1.3, NEGRO.TP, Q3.2 (S), U1.2 (GND), U7.2 (GND), U7.3 (EN)
unnamed: JP1.2, U1.1 (HYST)
unnamed: Q3.1 (G), R2.1, U1.5 (!OS)
unnamed: Q2.1 (G), Q3.3 (D), R1.1
unnamed: R3.2, U1.3 (VTEMP)
ROJO: C5.1, JP1.1, Q2.2 (S), R1.2, R2.2, ROJO.TP, U7.1 (VIN)
TEMP: R3.1, TP1.TP
VCC: Q2.3 (D)
VCC1: C4.1, C6.1, U1.4 (V+), U7.5 (VOUT)

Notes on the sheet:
3V (pq no tenian 3.3V en stock)

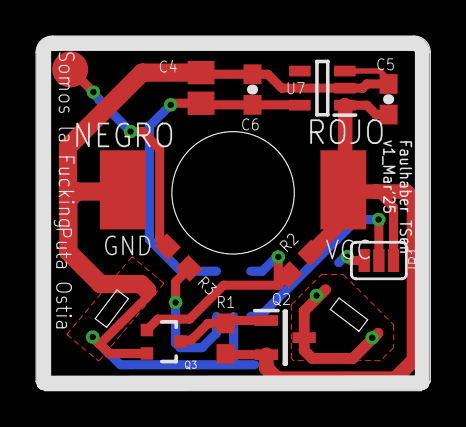
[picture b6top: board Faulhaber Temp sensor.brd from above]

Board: 2 copper layers, 21.9 x 19.7 mm, 14 parts (1 on the bottom side), 8 nets.

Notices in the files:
parts and their libraries:
SparkFun-Connectors: Licensing: Creative Commons ShareAlike 4.0 International - https://creativecommons.org/licenses/by-sa/4.0
COPYRIGHT: Copyright (C) 2022 Ultra Librarian. All rights reserved.
COPYRIGHT: Copyright (C) 2024 Ultra Librarian. All rights reserved.
